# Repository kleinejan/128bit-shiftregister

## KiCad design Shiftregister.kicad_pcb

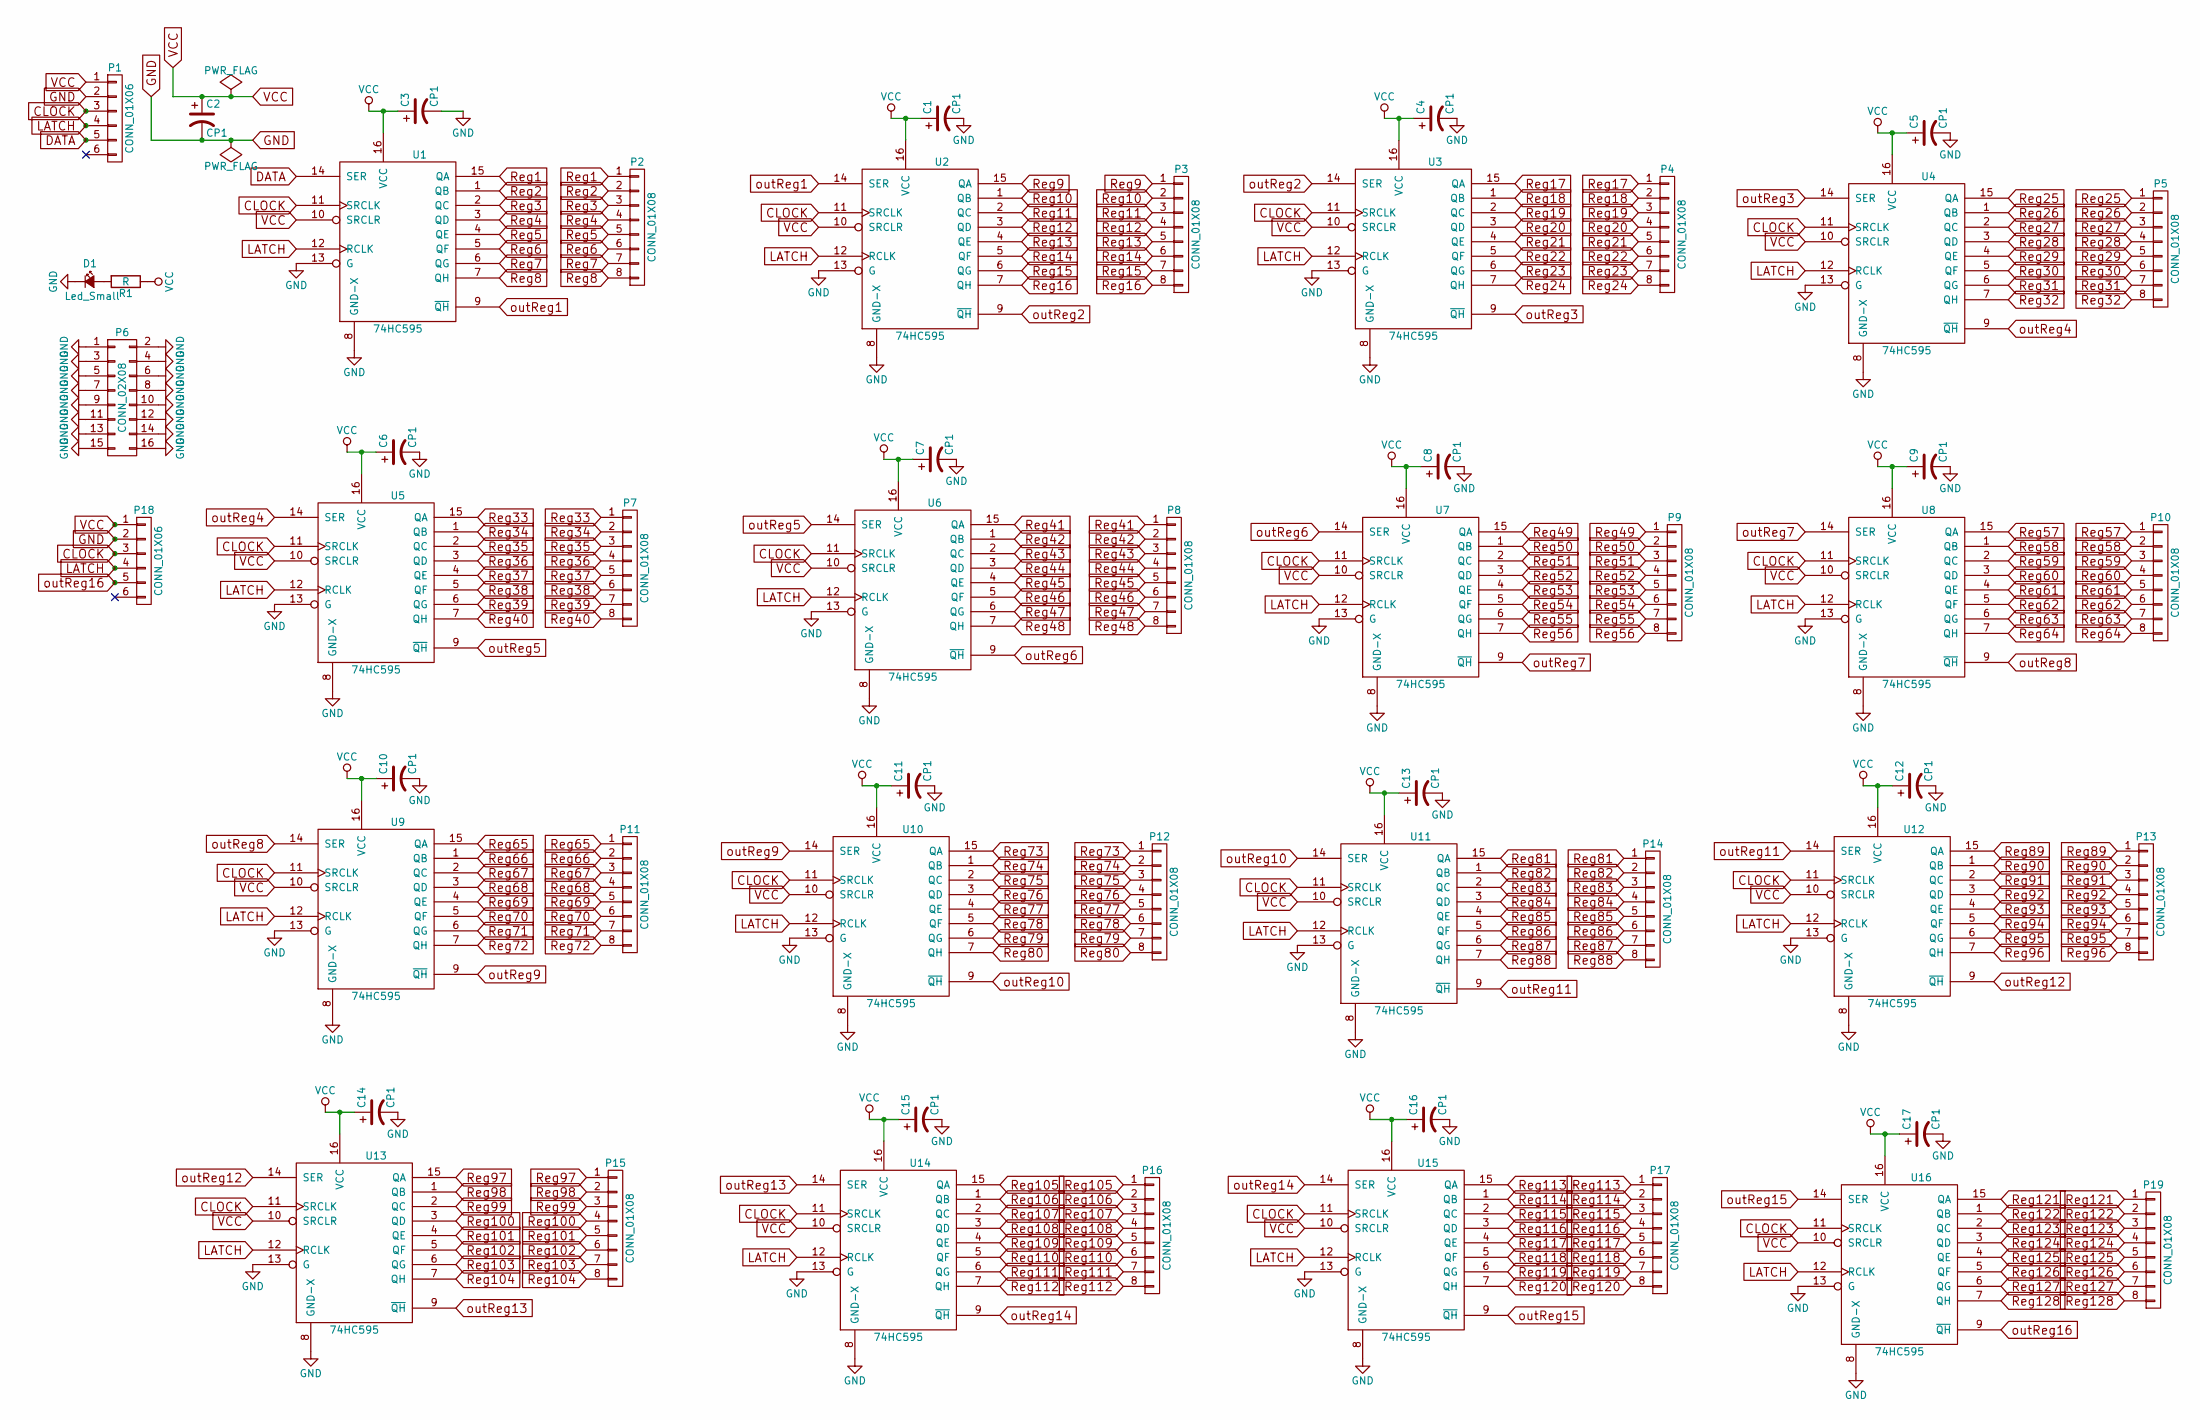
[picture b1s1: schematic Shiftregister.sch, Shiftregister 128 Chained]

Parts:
C1, C2, C3, C4, C5, C6, C7, C8, C9, C10, C11, C12, C13, C14, C15, C16, C17: CP1; CP_Tantalum_Case-X_EIA-7343-43_Reflow
D1: Led_Small; LED_0805_HandSoldering
P1, P18: CONN_01X06; Pin_Header_Straight_1x06_Pitch2.54mm
P2, P3, P4, P5, P7, P8, P9, P10, P11, P12, P13, P14, P15, P16, P17, P19: CONN_01X08; Pin_Header_Straight_1x08_Pitch2.54mm
P6: CONN_02X08; Pin_Header_Straight_2x08_Pitch2.54mm
R1: R; R_0805_HandSoldering
U1, U2, U3, U4, U5, U6, U7, U8, U9, U10, U11, U12, U13, U14, U15, U16: 74HC595; DIP-16_W7.62mm_Socket

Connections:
CLOCK: P1.3, P18.3, U1.11 (SRCLK), U2.11 (SRCLK), U3.11 (SRCLK), U4.11 (SRCLK), U5.11 (SRCLK), U6.11 (SRCLK), U7.11 (SRCLK), U8.11 (SRCLK), U9.11 (SRCLK), U10.11 (SRCLK), U11.11 (SRCLK), U12.11 (SRCLK), U13.11 (SRCLK), U14.11 (SRCLK), U15.11 (SRCLK), U16.11 (SRCLK); also elsewhere on the board
DATA: P1.5, U1.14 (SER); also elsewhere on the board
GND: C1.2, C2.2, C3.2, C4.2, C5.2, C6.2, C7.2, C8.2, C9.2, C10.2, C11.2, C12.2, C13.2, C14.2, C15.2, C16.2, C17.2, D1.1 (K), P1.2, P6.1, P6.2, P6.3, P6.4, P6.5, P6.6, P6.7, P6.8, P6.9, P6.10, P6.11, P6.12, P6.13, P6.14, P6.15, P6.16, P18.2, U1.8 (GND-X), U1.13 (G), U2.8 (GND-X), U2.13 (G), U3.8 (GND-X), U3.13 (G), U4.8 (GND-X), U4.13 (G), U5.8 (GND-X), U5.13 (G), U6.8 (GND-X), U6.13 (G), U7.8 (GND-X), U7.13 (G), U8.8 (GND-X), U8.13 (G), U9.8 (GND-X), U9.13 (G), U10.8 (GND-X), U10.13 (G), U11.8 (GND-X), U11.13 (G), U12.8 (GND-X), U12.13 (G), U13.8 (GND-X), U13.13 (G), U14.8 (GND-X), U14.13 (G), U15.8 (GND-X), U15.13 (G), U16.8 (GND-X), U16.13 (G); also elsewhere on the board
LATCH: P1.4, P18.4, U1.12 (RCLK), U2.12 (RCLK), U3.12 (RCLK), U4.12 (RCLK), U5.12 (RCLK), U6.12 (RCLK), U7.12 (RCLK), U8.12 (RCLK), U9.12 (RCLK), U10.12 (RCLK), U11.12 (RCLK), U12.12 (RCLK), U13.12 (RCLK), U14.12 (RCLK), U15.12 (RCLK), U16.12 (RCLK); also elsewhere on the board
unnamed: D1.2 (A), R1.2
Reg1: P2.1, U1.15 (QA)
Reg2: P2.2, U1.1 (QB)
Reg3: P2.3, U1.2 (QC)
Reg4: P2.4, U1.3 (QD)
Reg5: P2.5, U1.4 (QE)
Reg6: P2.6, U1.5 (QF)
Reg7: P2.7, U1.6 (QG)
Reg8: P2.8, U1.7 (QH)
Reg9: P3.1, U2.15 (QA)
Reg10: P3.2, U2.1 (QB)
Reg11: P3.3, U2.2 (QC)
Reg12: P3.4, U2.3 (QD)
Reg13: P3.5, U2.4 (QE)
Reg14: P3.6, U2.5 (QF)
Reg15: P3.7, U2.6 (QG)
Reg16: P3.8, U2.7 (QH)
Reg17: P4.1, U3.15 (QA)
Reg18: P4.2, U3.1 (QB)
Reg19: P4.3, U3.2 (QC)
Reg20: P4.4, U3.3 (QD)
Reg21: P4.5, U3.4 (QE)
Reg22: P4.6, U3.5 (QF)
Reg23: P4.7, U3.6 (QG)
Reg24: P4.8, U3.7 (QH)
Reg25: P5.1, U4.15 (QA)
Reg26: P5.2, U4.1 (QB)
Reg27: P5.3, U4.2 (QC)
Reg28: P5.4, U4.3 (QD)
Reg29: P5.5, U4.4 (QE)
Reg30: P5.6, U4.5 (QF)
Reg31: P5.7, U4.6 (QG)
Reg32: P5.8, U4.7 (QH)
Reg33: P7.1, U5.15 (QA)
Reg34: P7.2, U5.1 (QB)
Reg35: P7.3, U5.2 (QC)
Reg36: P7.4, U5.3 (QD)
Reg37: P7.5, U5.4 (QE)
Reg38: P7.6, U5.5 (QF)
Reg39: P7.7, U5.6 (QG)
Reg40: P7.8, U5.7 (QH)
Reg41: P8.1, U6.15 (QA)
Reg42: P8.2, U6.1 (QB)
Reg43: P8.3, U6.2 (QC)
Reg44: P8.4, U6.3 (QD)
Reg45: P8.5, U6.4 (QE)
Reg46: P8.6, U6.5 (QF)
Reg47: P8.7, U6.6 (QG)
Reg48: P8.8, U6.7 (QH)
Reg49: P9.1, U7.15 (QA)
Reg50: P9.2, U7.1 (QB)
Reg51: P9.3, U7.2 (QC)
Reg52: P9.4, U7.3 (QD)
Reg53: P9.5, U7.4 (QE)
Reg54: P9.6, U7.5 (QF)
Reg55: P9.7, U7.6 (QG)
Reg56: P9.8, U7.7 (QH)
Reg57: P10.1, U8.15 (QA)
Reg58: P10.2, U8.1 (QB)
Reg59: P10.3, U8.2 (QC)
Reg60: P10.4, U8.3 (QD)
Reg61: P10.5, U8.4 (QE)
Reg62: P10.6, U8.5 (QF)
Reg63: P10.7, U8.6 (QG)
Reg64: P10.8, U8.7 (QH)
Reg65: P11.1, U9.15 (QA)
Reg66: P11.2, U9.1 (QB)
Reg67: P11.3, U9.2 (QC)
Reg68: P11.4, U9.3 (QD)
Reg69: P11.5, U9.4 (QE)
Reg70: P11.6, U9.5 (QF)
Reg71: P11.7, U9.6 (QG)
Reg72: P11.8, U9.7 (QH)
Reg73: P12.1, U10.15 (QA)
Reg74: P12.2, U10.1 (QB)
Reg75: P12.3, U10.2 (QC)
Reg76: P12.4, U10.3 (QD)
Reg77: P12.5, U10.4 (QE)
Reg78: P12.6, U10.5 (QF)
Reg79: P12.7, U10.6 (QG)
Reg80: P12.8, U10.7 (QH)
Reg81: P14.1, U11.15 (QA)
Reg82: P14.2, U11.1 (QB)
Reg83: P14.3, U11.2 (QC)
Reg84: P14.4, U11.3 (QD)
Reg85: P14.5, U11.4 (QE)
Reg86: P14.6, U11.5 (QF)
Reg87: P14.7, U11.6 (QG)
Reg88: P14.8, U11.7 (QH)
Reg89: P13.1, U12.15 (QA)
Reg90: P13.2, U12.1 (QB)
Reg91: P13.3, U12.2 (QC)
Reg92: P13.4, U12.3 (QD)
Reg93: P13.5, U12.4 (QE)
Reg94: P13.6, U12.5 (QF)
Reg95: P13.7, U12.6 (QG)
Reg96: P13.8, U12.7 (QH)
Reg97: P15.1, U13.15 (QA)
Reg98: P15.2, U13.1 (QB)
Reg99: P15.3, U13.2 (QC)
Reg100: P15.4, U13.3 (QD)
Reg101: P15.5, U13.4 (QE)
Reg102: P15.6, U13.5 (QF)
Reg103: P15.7, U13.6 (QG)
Reg104: P15.8, U13.7 (QH)
Reg105: P16.1, U14.15 (QA)
Reg106: P16.2, U14.1 (QB)
Reg107: P16.3, U14.2 (QC)
Reg108: P16.4, U14.3 (QD)
Reg109: P16.5, U14.4 (QE)
Reg110: P16.6, U14.5 (QF)
Reg111: P16.7, U14.6 (QG)
Reg112: P16.8, U14.7 (QH)
Reg113: P17.1, U15.15 (QA)
Reg114: P17.2, U15.1 (QB)
Reg115: P17.3, U15.2 (QC)
Reg116: P17.4, U15.3 (QD)
Reg117: P17.5, U15.4 (QE)
Reg118: P17.6, U15.5 (QF)
Reg119: P17.7, U15.6 (QG)
Reg120: P17.8, U15.7 (QH)
Reg121: P19.1, U16.15 (QA)
Reg122: P19.2, U16.1 (QB)
Reg123: P19.3, U16.2 (QC)
Reg124: P19.4, U16.3 (QD)
Reg125: P19.5, U16.4 (QE)
Reg126: P19.6, U16.5 (QF)
Reg127: P19.7, U16.6 (QG)
Reg128: P19.8, U16.7 (QH)
VCC: C1.1, C2.1, C3.1, C4.1, C5.1, C6.1, C7.1, C8.1, C9.1, C10.1, C11.1, C12.1, C13.1, C14.1, C15.1, C16.1, C17.1, P1.1, P18.1, R1.1, U1.10 (SRCLR), U1.16 (VCC), U2.10 (SRCLR), U2.16 (VCC), U3.10 (SRCLR), U3.16 (VCC), U4.10 (SRCLR), U4.16 (VCC), U5.10 (SRCLR), U5.16 (VCC), U6.10 (SRCLR), U6.16 (VCC), U7.10 (SRCLR), U7.16 (VCC), U8.10 (SRCLR), U8.16 (VCC), U9.10 (SRCLR), U9.16 (VCC), U10.10 (SRCLR), U10.16 (VCC), U11.10 (SRCLR), U11.16 (VCC), U12.10 (SRCLR), U12.16 (VCC), U13.10 (SRCLR), U13.16 (VCC), U14.10 (SRCLR), U14.16 (VCC), U15.10 (SRCLR), U15.16 (VCC), U16.10 (SRCLR), U16.16 (VCC); also elsewhere on the board
outReg1: U1.9 (~QH), U2.14 (SER)
outReg2: U2.9 (~QH), U3.14 (SER)
outReg3: U3.9 (~QH), U4.14 (SER)
outReg4: U4.9 (~QH), U5.14 (SER)
outReg5: U5.9 (~QH), U6.14 (SER)
outReg6: U6.9 (~QH), U7.14 (SER)
outReg7: U7.9 (~QH), U8.14 (SER)
outReg8: U8.9 (~QH), U9.14 (SER)
outReg9: U9.9 (~QH), U10.14 (SER)
outReg10: U10.9 (~QH), U11.14 (SER)
outReg11: U11.9 (~QH), U12.14 (SER)
outReg12: U12.9 (~QH), U13.14 (SER)
outReg13: U13.9 (~QH), U14.14 (SER)
outReg14: U14.9 (~QH), U15.14 (SER)
outReg15: U15.9 (~QH), U16.14 (SER)
outReg16: P18.5, U16.9 (~QH); also elsewhere on the board

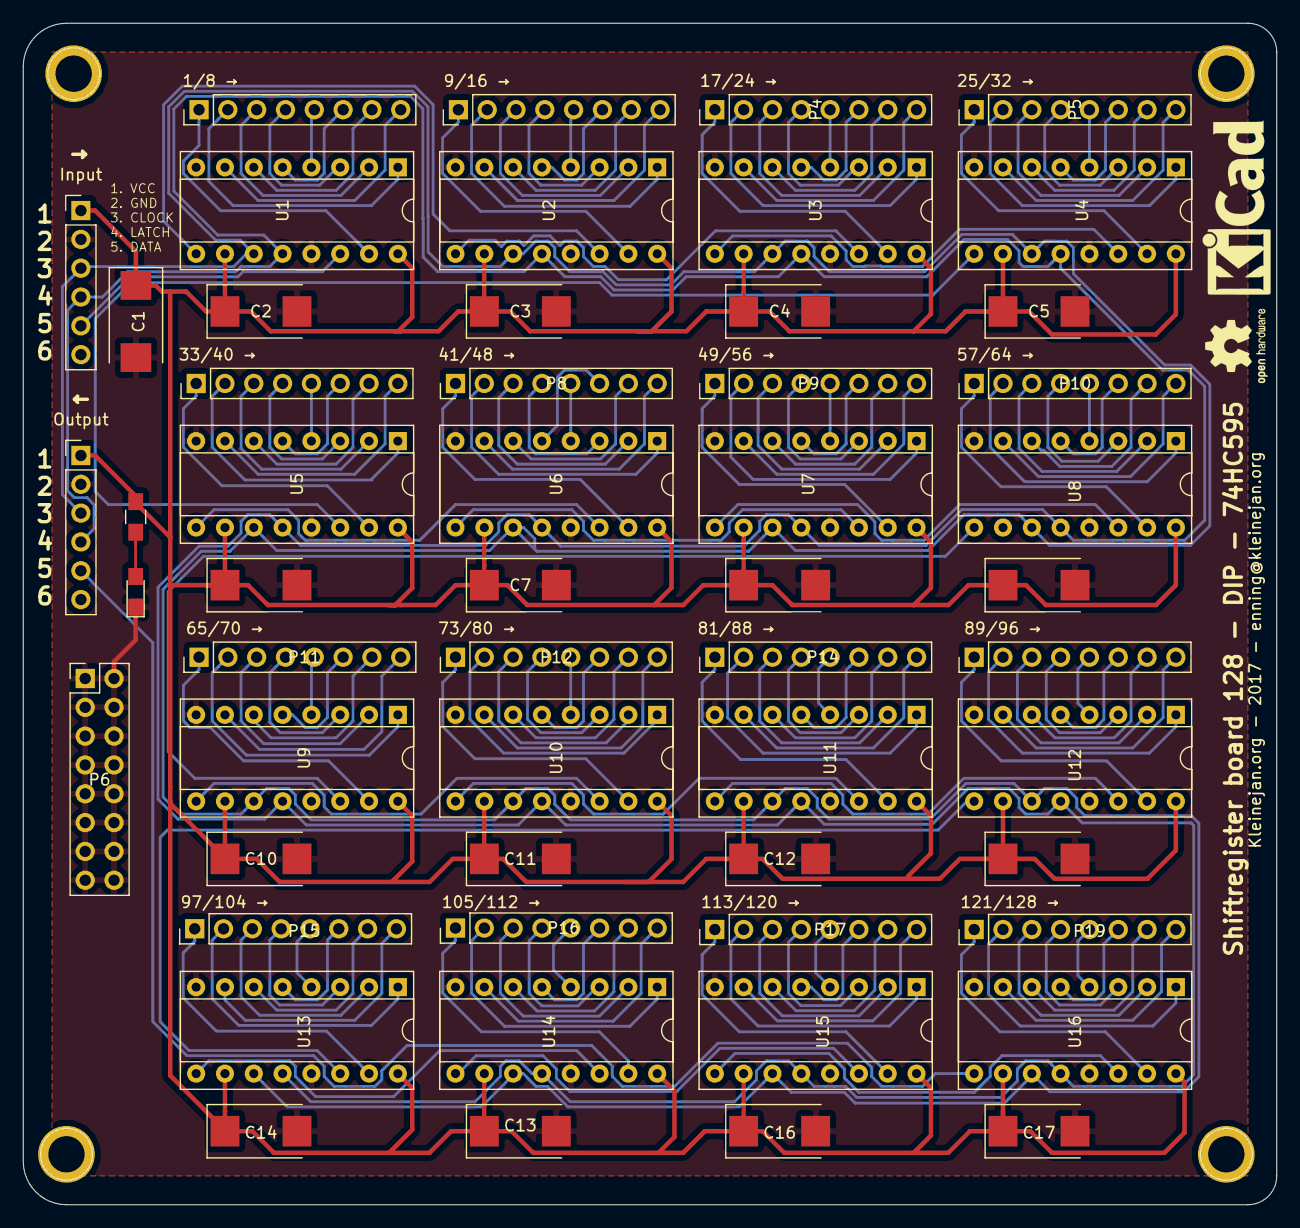
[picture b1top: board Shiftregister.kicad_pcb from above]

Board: 2 copper layers, 110.5 x 104.1 mm, 54 parts (0 on the bottom side), 150 nets.

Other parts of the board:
Input: CONN_01X06; Pin_Header_Straight_1x06_Pitch2.54mm
Output: CONN_01X06; Pin_Header_Straight_1x06_Pitch2.54mm

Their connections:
CLOCK: Input.3, Output.3; also elsewhere on the board
DATA: Input.5; also elsewhere on the board
GND: Input.2, Output.2; also elsewhere on the board
LATCH: Input.4, Output.4; also elsewhere on the board
VCC: Input.1, Output.1; also elsewhere on the board
outReg16: Output.5; also elsewhere on the board

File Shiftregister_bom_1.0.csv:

Component,Description,Part,References,Value,Footprint,Quantity Per PCB,Datasheet
1,Polarised capacitor,CP1,C2,100UF,CP_Tantalum_Case-X_EIA-7343-43_Reflow,1,
2,Polarised capacitor,CP1,C1 C3 C4 C5 C6 C7 C8 C9 C10 C11 C12 C13 C14 C15 C16 C17,10UF,CP_Tantalum_Case-X_EIA-7343-43_Reflow,16,
3,Led,Led_Small,D1,Led_Small,LED_0805_HandSoldering,1,
4,"Connector, single row, 01x06",CONN_01X06,P1 P18,CONN_01X06,Pin_Header_Straight_1x06_Pitch2.54mm,2,
5,"Connector, single row, 01x08",CONN_01X08,P2 P3 P4 P5 P7 P8 P9 P10 P11 P12 P13 P14 P15 P16 P17 P19,CONN_01X08,Pin_Header_Straight_1x08_Pitch2.54mm,16,
6,"Connector, double row, 02x08",CONN_02X08,P6,CONN_02X08,Pin_Header_Straight_2x08_Pitch2.54mm,1,
7,Resistor,R,R1,R,R_0805_HandSoldering,1,
8,8 bits serial in // out Shift Register 3 State Out,74HC595,U1 U2 U3 U4 U5 U6 U7 U8 U9 U10 U11 U12 U13 U14 U15 U16,74HC595,DIP-16_W7.62mm_Socket,16,74xx/74HC595.pdf





Component Groups:,8
Component Count:,54
Fitted Components:,54
Number of PCBs:,1
Total components:,54
Schematic Version:,1.0
Schematic Date:,2017-01-08
BoM Date:,"2018 May 08, Tuesday 22:25:03"
Schematic Source:,/Users/janneman/128bit-shiftregister/Shiftregister.sch
KiCad Version:,Eeschema 4.0.4-stable

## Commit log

2018-03-07 init
2018-05-08 Added BOM
2018-05-08 Updated BOM with resistor value
2018-05-08 fiddle
